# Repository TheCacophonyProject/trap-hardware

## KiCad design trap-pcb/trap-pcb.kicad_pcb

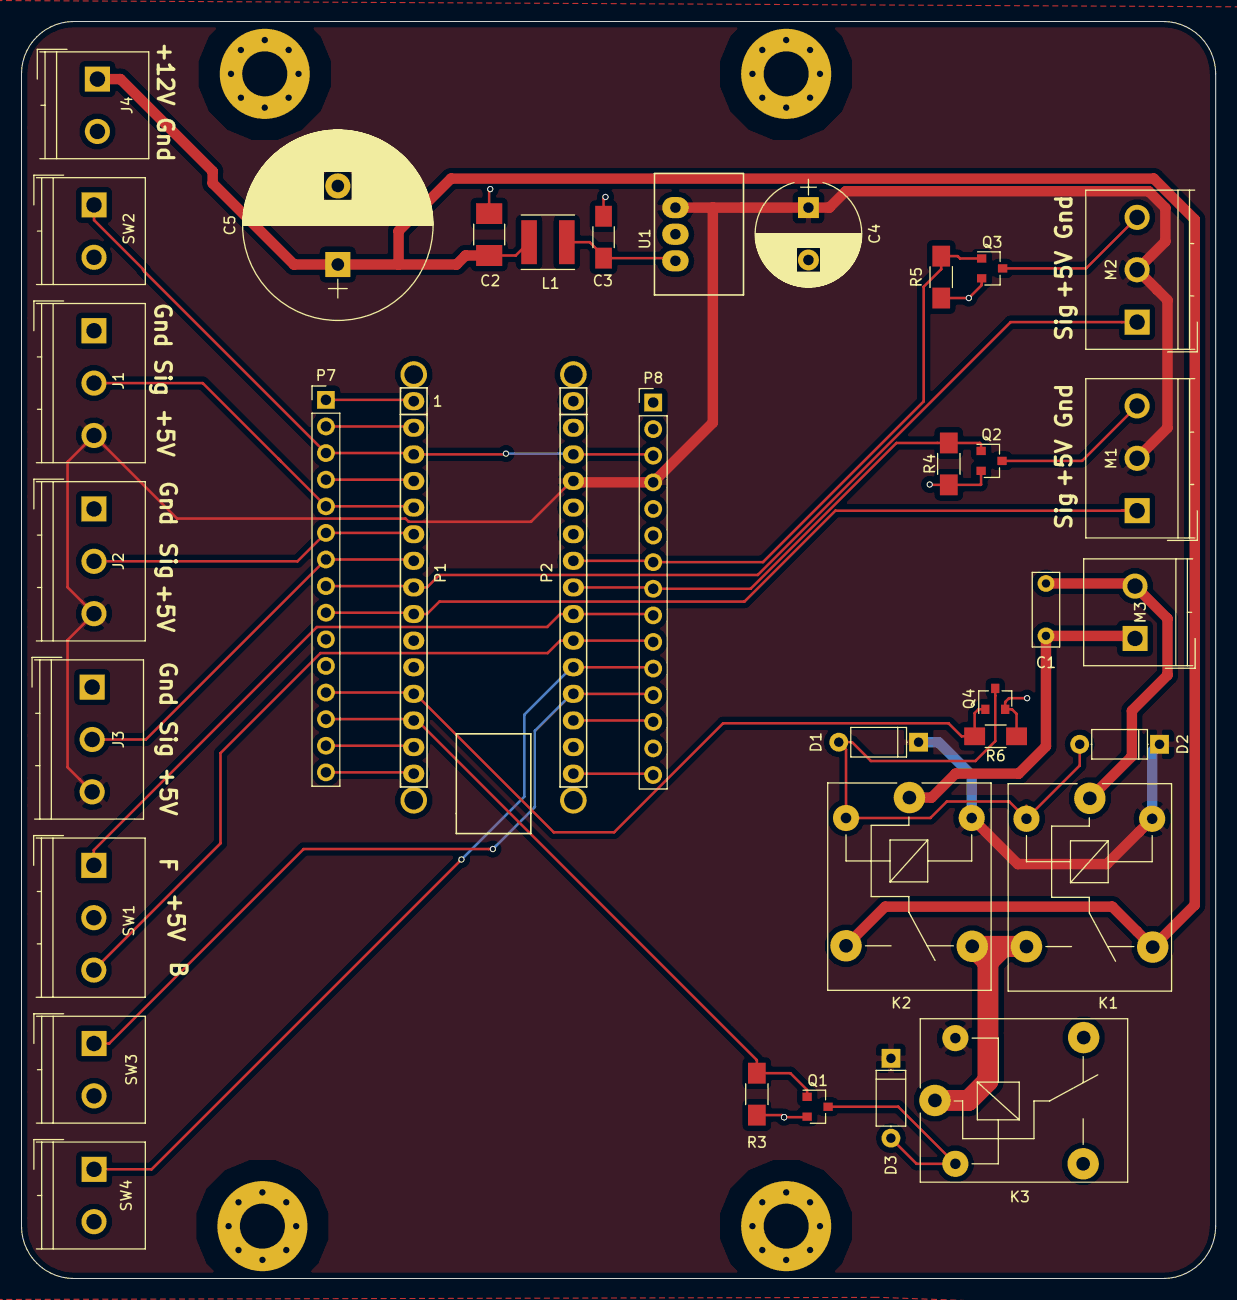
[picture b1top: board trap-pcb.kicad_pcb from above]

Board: 2 copper layers, 114.0 x 120.0 mm, 44 parts (0 on the bottom side), 31 nets.

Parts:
C1: C; C_Rect_L7.0mm_W2.5mm_P5.00mm
C2: 10uF; C_1210_HandSoldering
C3: 4.7uF; C_1206_HandSoldering
C4: 820uF; CP_Radial_D10.0mm_P5.00mm
C5: 6800uF; CP_Radial_D18.0mm_P7.50mm
D1, D2, D3: D; D_A-405_P7.62mm_Horizontal
J1: PIR_1; TerminalBlock_Philmore_TB133_03x5mm_Straight
J2: PIR_2; TerminalBlock_Philmore_TB133_03x5mm_Straight
J3: PIR_3; TerminalBlock_Philmore_TB133_03x5mm_Straight
J4: Power In; TerminalBlock_Philmore_TB132_02x5mm_Straight
K1, K2, K3: RELAY; Relay_SPDT_SANYOU_SRD_Series_Form_C
L1: 10uH; L_Taiyo-Yuden_MD-5050
M1: Motor_Servo_1; TerminalBlock_Philmore_TB133_03x5mm_Straight
M2: Motor_Servo_2; TerminalBlock_Philmore_TB133_03x5mm_Straight
M3: Motor_DC; TerminalBlock_Philmore_TB132_02x5mm_Straight
MK1, MK2, MK3, MK4: Mounting_Hole; MountingHole_4.3mm_M4_Pad_Via
P1: Digital; Socket_Strip_Arduino_1x15
P2: Analog; Socket_Strip_Arduino_1x15
P3, P4, P5, P6: CONN_01X01; 1pin_Nano
P7: Digital; Pin_Header_Straight_1x15_Pitch2.54mm
P8: Analog; Pin_Header_Straight_1x15_Pitch2.54mm
Q1, Q2, Q3, Q4: Q_NMOS_GSD; SOT-23
R3, R4, R5, R6: 100k; R_1206_HandSoldering
SW1: Motor_controll; TerminalBlock_Philmore_TB133_03x5mm_Straight
SW2: Reset; TerminalBlock_Philmore_TB132_02x5mm_Straight
SW3: Extended; TerminalBlock_Philmore_TB132_02x5mm_Straight
SW4: Retracted; TerminalBlock_Philmore_TB132_02x5mm_Straight
U1: R-78B5.0-2.0; DCDC-Conv_Recom_R-78HBxx-0.5

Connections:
+5V: C4.1, D1.1, D2.1, D3.1, J1.3, J2.3, J3.3, K1.2, K2.2, K3.2, M1.2, M2.2, P2.4, P8.4, U1.3
/0(Rx): P1.2, P7.2
/1(Tx): P1.1, P7.1
/11(**/MOSI): P1.14, P7.14
/12(MISO): P1.15, P7.15
/13(SCK): P2.15, P8.15
/AREF: P2.13, P8.13
/Extended: P2.12, P8.12, SW3.1
/H_bridge_back: P1.12, P7.12, Q4.1, R6.1
/H_bridge_on: P1.13, P7.13, Q1.1, R3.1
/Motor_back: P2.10, P8.10, SW1.3
/Motor_forward: P2.9, P8.9, SW1.1
/PIR_1: J1.2, P1.5, P7.5
/PIR_2: J2.2, P1.6, P7.6
/PIR_3: J3.2, P1.7, P7.7
/Reset: P1.3, P2.3, P7.3, P8.3, SW2.1
/Retracted: P2.11, P8.11, SW4.1
/Servo_1_PWM: M2.1, P1.8, P7.8
/Servo_1_power: P2.7, P8.7, Q3.1, R5.1
/Servo_2_PWM: M1.1, P1.9, P7.9
/Servo_2_power: P2.8, P8.8, Q2.1, R4.1
GND: C2.2, C3.2, C4.2, C5.2, J1.1, J2.1, J3.1, J4.2, K3.5, P1.4, P2.2, P7.4, P8.2, Q1.2, Q2.2, Q3.2, Q4.2, R3.2, R4.2, R5.2, R6.2, SW1.2, SW2.2, SW3.2, SW4.2, U1.2
unnamed: C1.1, K2.1, M3.1
unnamed: C1.2, K1.1, M3.2
unnamed: C3.1, L1.2, U1.1
unnamed: D1.2, D2.2, K1.3, K2.3, Q4.3
unnamed: D3.2, K3.3, Q1.3
unnamed: K1.5, K2.4, K3.1
unnamed: M1.3, Q2.3
unnamed: M2.3, Q3.3
VCC: C2.1, C5.1, J4.1, K1.4, K2.5, L1.1

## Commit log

2018-11-27 updated pcb
